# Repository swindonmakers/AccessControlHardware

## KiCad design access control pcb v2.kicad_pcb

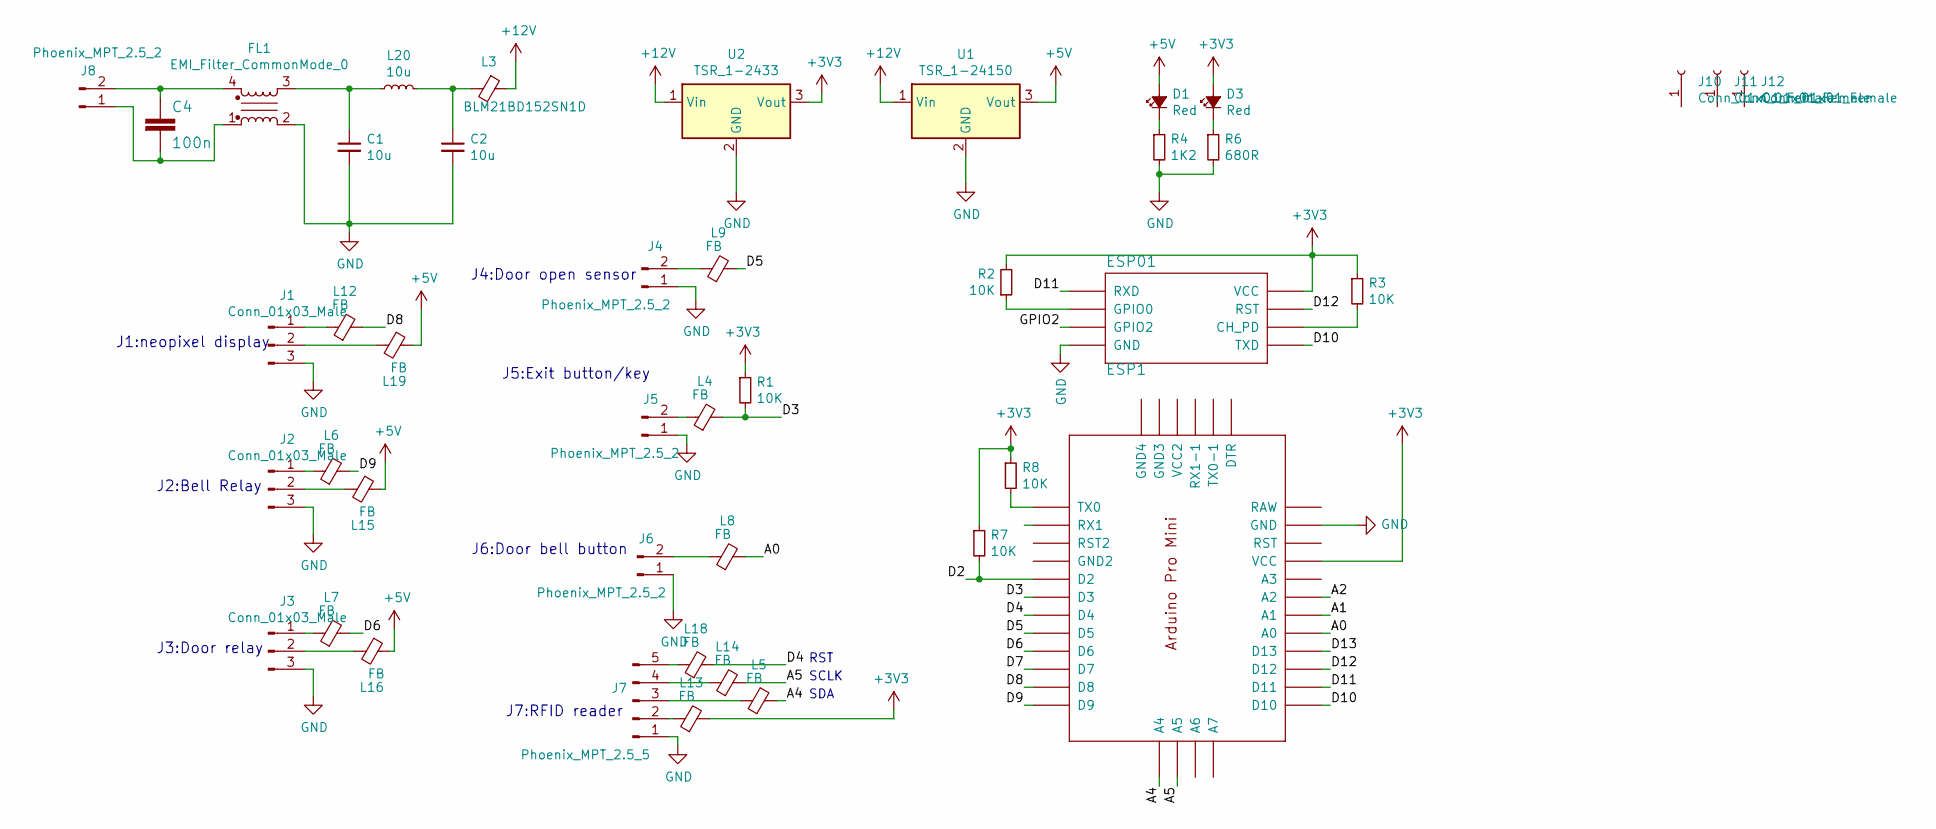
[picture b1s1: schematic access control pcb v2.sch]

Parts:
C1, C2: 10u; C_0805_2012Metric
C4: 100n; C_0805_2012Metric
D1, D3: Red; LED_1206_3216Metric
ESP1: ESP01
FL1: EMI_Filter_CommonMode_0; CommonModeChoke_WuerthType-WE-CMB_Size-XS
J1, J2, J3: Conn_01x03_Male; JST_XH_B03B-XH-A_1x03_P2.50mm_Vertical
J4, J5, J6: Phoenix_MPT_2.5_2; JST_XH_B02B-XH-A_1x02_P2.50mm_Vertical
J7: Phoenix_MPT_2.5_5; JST_XH_B05B-XH-A_1x05_P2.50mm_Vertical
J8: Phoenix_MPT_2.5_2; PhoenixContact_MSTBA_2,5_2-G-5,08_1x02_P5.08mm_Horizontal
J10, J11, J12: Conn_01x01_Female; MountingHole_3mm
L3: BLM21BD152SN1D; L_0805_2012Metric
L4, L5, L6, L7, L8, L9, L12, L13, L14, L15, L16, L18, L19: FB; L_0805_2012Metric
L20: 10u; L_0805_2012Metric
R1, R2, R3, R7, R8: 10K; R_0805_2012Metric
R4: 1K2; R_0805_2012Metric
R6: 680R; R_0805_2012Metric
U1: TSR_1-24150; Converter_DCDC_TRACO_TSR-1_THT
U2: TSR_1-2433; Converter_DCDC_TRACO_TSR-1_THT
U$1: PRO-MINI

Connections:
+3V3: D3.2 (A), ESP1.VCC, L13.2, R1.1, R2.2, R3.1, R7.1, R8.1, U2.3 (Vout), U$1.VCC
+5V: D1.2 (A), L15.1, L16.1, L19.1, U1.3 (Vout)
+12V: L3.1, U1.1 (Vin), U2.1 (Vin)
/A0: L8.2, U$1.A0
/A1: U$1.A1
/A2: U$1.A2
/A4: L5.2, U$1.A4
/A5: L14.2, U$1.A5
/D2: R7.2, U$1.D2
/D3: L4.2, R1.2, U$1.D3
/D4: L18.2, U$1.D4
/D5: L9.2, U$1.D5
/D6: L7.2, U$1.D6
/D7: U$1.D7
/D8: L12.2, U$1.D8
/D9: L6.2, U$1.D9
/D10: ESP1.TX (TXD), U$1.D10
/D11: ESP1.RX (RXD), U$1.D11
/D12: ESP1.RST, U$1.D12
/D13: U$1.D13
/GPIO2: ESP1.GPIO2
GND: C1.2, C2.2, ESP1.GND, FL1.2, J1.3, J2.3, J3.3, J4.1, J5.1, J6.1, J7.1, R4.2, R6.2, U1.2 (GND), U2.2 (GND), U$1.GND
unnamed: C1.1, FL1.3, L20.1
unnamed: C2.1, L3.2, L20.2
unnamed: C4.1, FL1.4, J8.2
unnamed: C4.2, FL1.1, J8.1
unnamed: D1.1 (K), R4.1
unnamed: D3.1 (K), R6.1
unnamed: ESP1.CH_PD, R3.2
unnamed: ESP1.GPIO0, R2.1
unnamed: J1.1, L12.1
unnamed: J1.2, L19.2
unnamed: J2.1, L6.1
unnamed: J2.2, L15.2
unnamed: J3.1, L7.1
unnamed: J3.2, L16.2
unnamed: J4.2, L9.1
unnamed: J5.2, L4.1
unnamed: J6.2, L8.1
unnamed: J7.2, L13.1
unnamed: J7.3, L5.1
unnamed: J7.4, L14.1
unnamed: J7.5, L18.1
unnamed: R8.2, U$1.TX0

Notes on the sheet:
J2:Bell Relay
J3:Door relay
J1:neopixel display
J4:Door open sensor
J7:RFID reader
J5:Exit button/key
J6:Door bell button
RST
SCLK
SDA

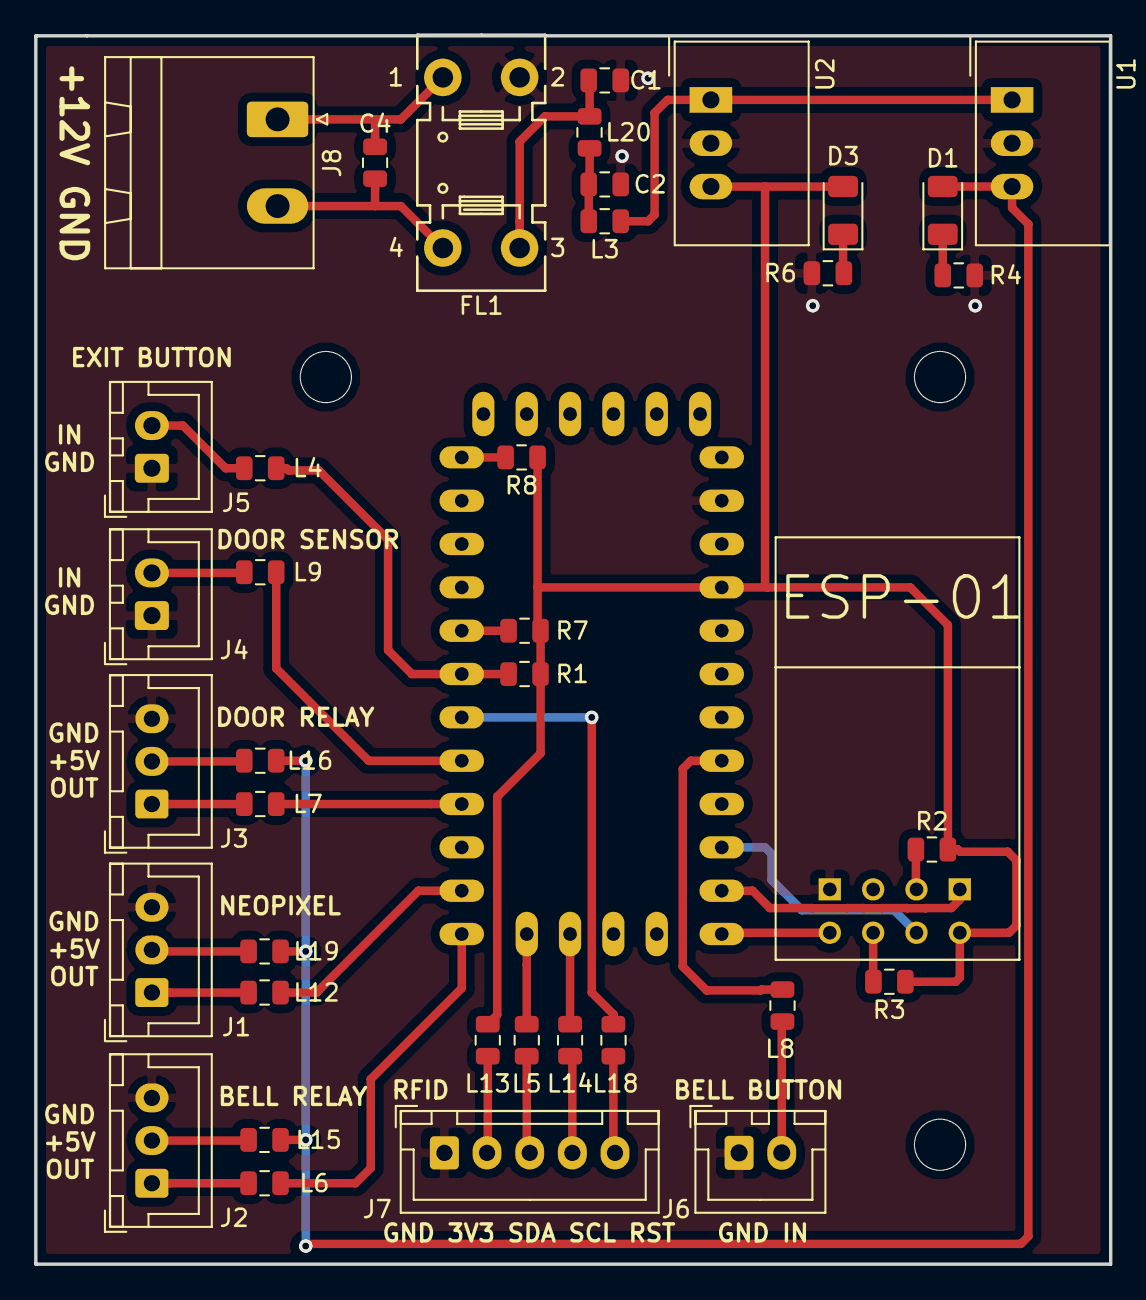
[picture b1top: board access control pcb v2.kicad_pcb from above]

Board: 2 copper layers, 63.0 x 72.0 mm, 43 parts (0 on the bottom side), 39 nets.
